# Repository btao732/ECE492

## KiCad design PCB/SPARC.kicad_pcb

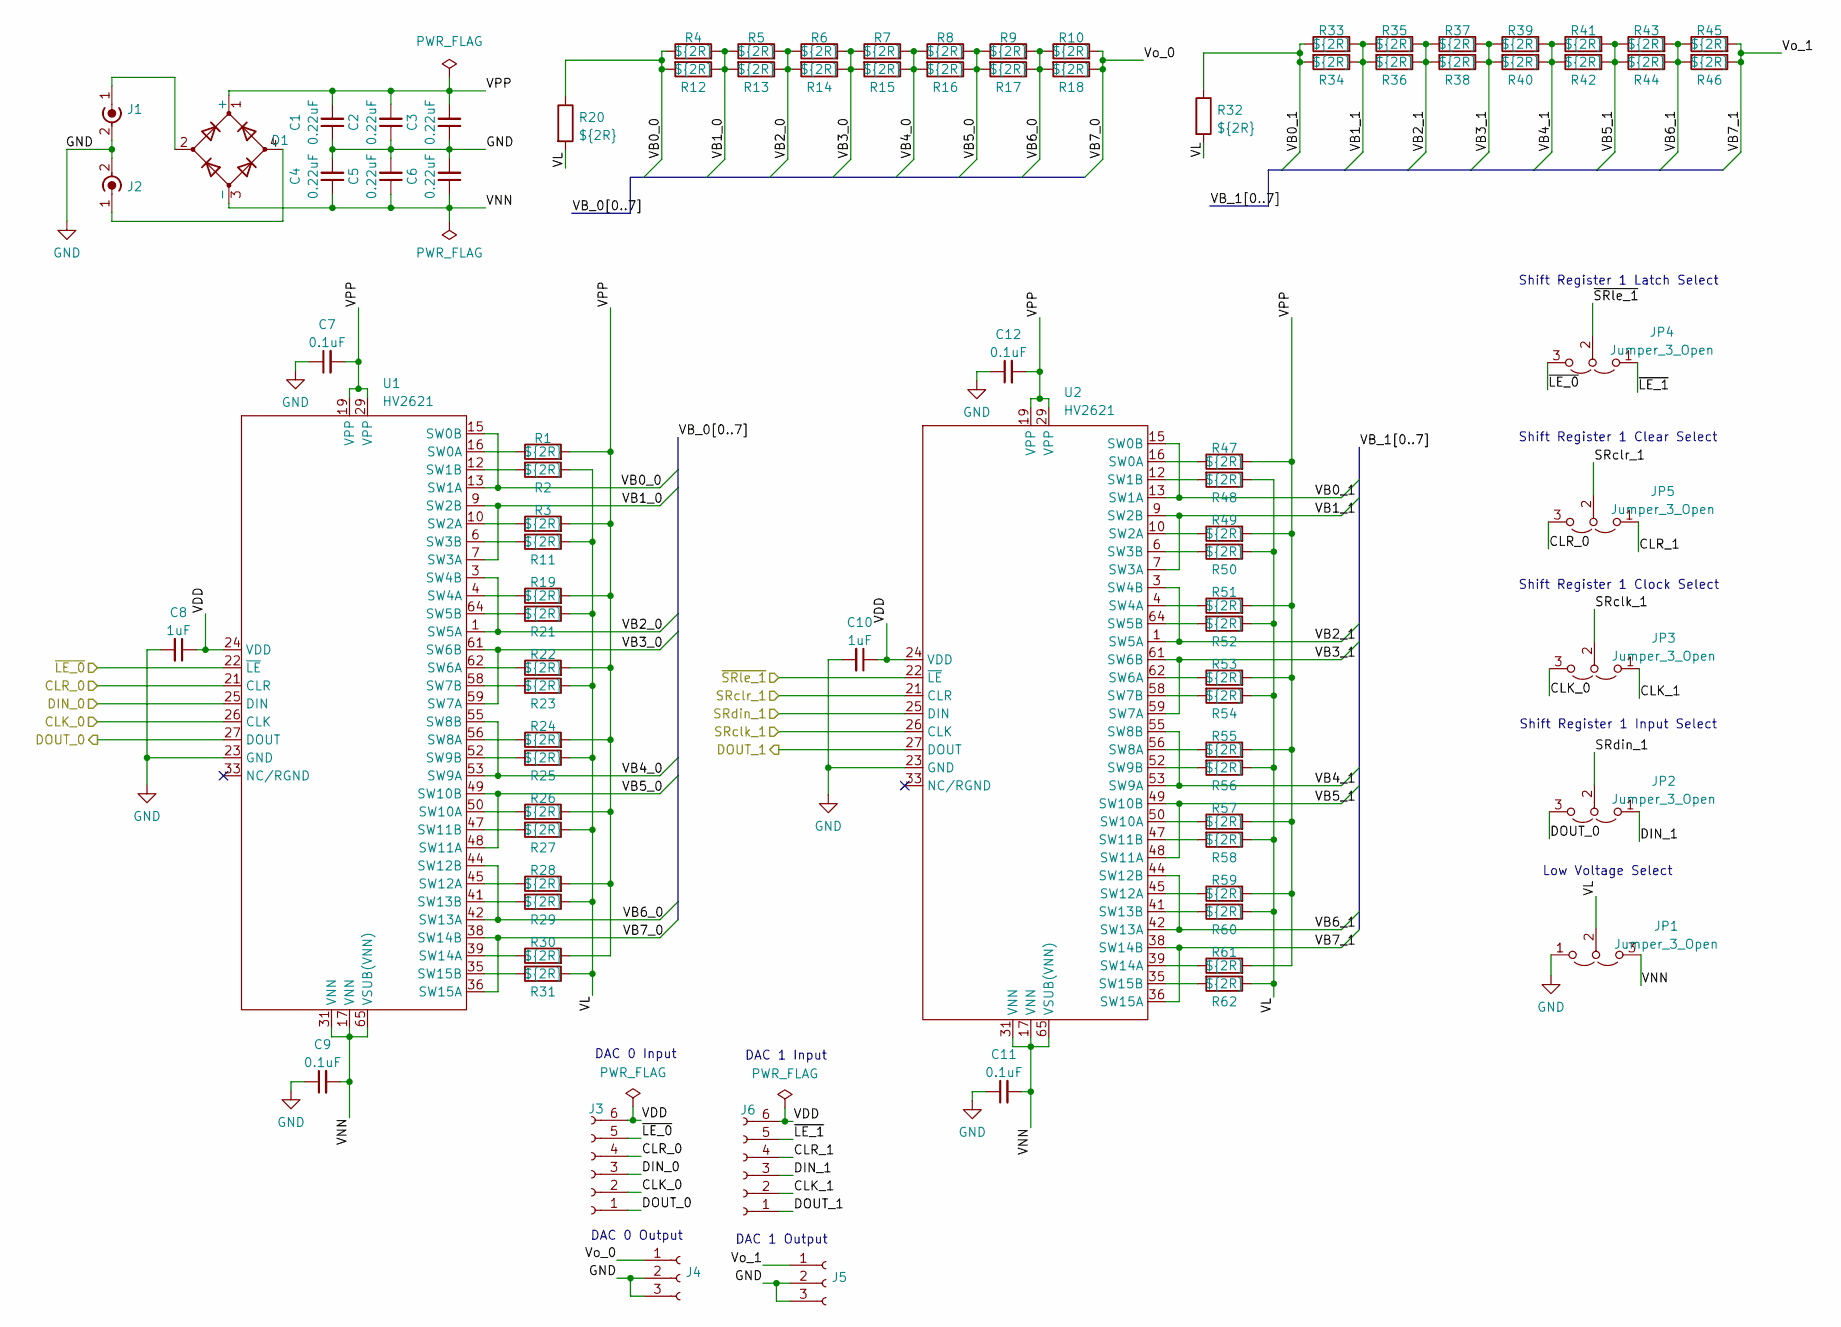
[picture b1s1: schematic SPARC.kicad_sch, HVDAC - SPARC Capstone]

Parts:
C1, C2, C3, C4, C5, C6: 0.22uF; C_1210_3225Metric
C7, C9, C11, C12: 0.1uF; C_1210_3225Metric_Pad1.33x2.70mm_HandSolder
C8, C10: 1uF; C_0603_1608Metric
D1: D_Bridge_+A-A; Package_HDS
J1, J2: Conn_Coaxial_Power; SMA_Molex_73251-1153_EdgeMount_Horizontal
J3, J6: Conn_01x06_Female; PinHeader_1x06_P2.54mm_Vertical
J4, J5: Conn_01x03_Female; PinHeader_1x03_P2.54mm_Vertical
JP1, JP2, JP3, JP4, JP5: Jumper_3_Open; PinHeader_1x03_P2.54mm_Vertical
R1, R2, R3, R4, R5, R6, R7, R8, R9, R10, R11, R12, R13, R14, R15, R16, R17, R18, R19, R20, R21, R22, R23, R24, R25, R26, R27, R28, R29, R30, R31, R32, R33, R34, R35, R36, R37, R38, R39, R40, R41, R42, R43, R44, R45, R46, R47, R48, R49, R50, R51, R52, R53, R54, R55, R56, R57, R58, R59, R60, R61, R62: ${2R}; R_0603_1608Metric_small_silk
U1, U2: HV2621; VQFN-64-1EP_9x9mm_P0.5mm_EP7.15x7.15mm_ThermalVias_0.25mm

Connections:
/CLK_0: J3.2, JP3.3 (B), U1.26 (CLK); also elsewhere on the board
/CLK_1: J6.2, JP3.1 (A); also elsewhere on the board
/CLR_0: J3.4, JP5.3 (B), U1.21 (CLR); also elsewhere on the board
/CLR_1: J6.4, JP5.1 (A); also elsewhere on the board
/DIN_0: J3.3, U1.25 (DIN)
/DIN_1: J6.3, JP2.1 (A); also elsewhere on the board
/DOUT_0: J3.1, JP2.3 (B), U1.27 (DOUT); also elsewhere on the board
/DOUT_1: J6.1, U2.27 (DOUT)
/SRclk_1: U2.26 (CLK); also elsewhere on the board
/SRclr_1: U2.21 (CLR); also elsewhere on the board
/SRdin_1: U2.25 (DIN); also elsewhere on the board
/VB0_0: R4.1, R12.2, R20.1, U1.13 (SW1A), U1.15 (SW0B)
/VB0_1: R32.1, R33.1, R34.2, U2.13 (SW1A), U2.15 (SW0B)
/VB1_0: R4.2, R5.1, R12.1, R13.2, U1.7 (SW3A), U1.9 (SW2B)
/VB1_1: R33.2, R34.1, R35.1, R36.2, U2.7 (SW3A), U2.9 (SW2B)
/VB2_0: R5.2, R6.1, R13.1, R14.2, U1.1 (SW5A), U1.3 (SW4B)
/VB2_1: R35.2, R36.1, R37.1, R38.2, U2.1 (SW5A), U2.3 (SW4B)
/VB3_0: R6.2, R7.1, R14.1, R15.2, U1.59 (SW7A), U1.61 (SW6B)
/VB3_1: R37.2, R38.1, R39.1, R40.2, U2.59 (SW7A), U2.61 (SW6B)
/VB4_0: R7.2, R8.1, R15.1, R16.2, U1.53 (SW9A), U1.55 (SW8B)
/VB4_1: R39.2, R40.1, R41.1, R42.2, U2.53 (SW9A), U2.55 (SW8B)
/VB5_0: R8.2, R9.1, R16.1, R17.2, U1.48 (SW11A), U1.49 (SW10B)
/VB5_1: R41.2, R42.1, R43.1, R44.2, U2.48 (SW11A), U2.49 (SW10B)
/VB6_0: R9.2, R10.1, R17.1, R18.2, U1.42 (SW13A), U1.44 (SW12B)
/VB6_1: R43.2, R44.1, R45.1, R46.2, U2.42 (SW13A), U2.44 (SW12B)
/VB7_0: J4.1, R10.2, R18.1, U1.36 (SW15A), U1.38 (SW14B)
/VB7_1: J5.1, R45.2, R46.1, U2.36 (SW15A), U2.38 (SW14B)
/VDD: C8.1, C10.1, J3.6, J6.6, U1.24 (VDD), U2.24 (VDD)
/VL: JP1.2 (C), R2.1, R11.1, R20.2, R21.1, R23.1, R25.1, R27.1, R29.1, R31.1, R32.2, R48.1, R50.1, R52.1, R54.1, R56.1, R58.1, R60.1, R62.1
/VNN: C4.1, C5.1, C6.1, C9.2, C11.2, D1.3 (-), JP1.3 (B), U1.17 (VNN), U1.31 (VNN), U1.65 (VSUB(VNN)), U2.17 (VNN), U2.31 (VNN), U2.65 (VSUB(VNN))
/VPP: C1.2, C2.2, C3.2, C7.2, C12.2, D1.1 (+), R1.2, R3.2, R19.2, R22.2, R24.2, R26.2, R28.2, R30.2, R47.2, R49.2, R51.2, R53.2, R55.2, R57.2, R59.2, R61.2, U1.19 (VPP), U1.29 (VPP), U2.19 (VPP), U2.29 (VPP)
/~LE_0: J3.5, JP4.3 (B), U1.22 (~LE); also elsewhere on the board
/~LE_1: J6.5, JP4.1 (A); also elsewhere on the board
/~SRle_1: U2.22 (~LE); also elsewhere on the board
GND: C1.1, C2.1, C3.1, C4.2, C5.2, C6.2, C7.1, C8.2, C9.1, C10.2, C11.1, C12.1, J1.2 (Ext), J2.2 (Ext), J4.2, J4.3, J5.2, J5.3, JP1.1 (A), U1.23 (GND), U2.23 (GND)
unnamed: D1.2, J1.1 (In)
unnamed: D1.4, J2.1 (In)
unnamed: R1.1, U1.16 (SW0A)
unnamed: R2.2, U1.12 (SW1B)
unnamed: R3.1, U1.10 (SW2A)
unnamed: R11.2, U1.6 (SW3B)
unnamed: R19.1, U1.4 (SW4A)
unnamed: R21.2, U1.64 (SW5B)
unnamed: R22.1, U1.62 (SW6A)
unnamed: R23.2, U1.58 (SW7B)
unnamed: R24.1, U1.56 (SW8A)
unnamed: R25.2, U1.52 (SW9B)
unnamed: R26.1, U1.50 (SW10A)
unnamed: R27.2, U1.47 (SW11B)
unnamed: R28.1, U1.45 (SW12A)
unnamed: R29.2, U1.41 (SW13B)
unnamed: R30.1, U1.39 (SW14A)
unnamed: R31.2, U1.35 (SW15B)
unnamed: R47.1, U2.16 (SW0A)
unnamed: R48.2, U2.12 (SW1B)
unnamed: R49.1, U2.10 (SW2A)
unnamed: R50.2, U2.6 (SW3B)
unnamed: R51.1, U2.4 (SW4A)
unnamed: R52.2, U2.64 (SW5B)
unnamed: R53.1, U2.62 (SW6A)
unnamed: R54.2, U2.58 (SW7B)
unnamed: R55.1, U2.56 (SW8A)
unnamed: R56.2, U2.52 (SW9B)
unnamed: R57.1, U2.50 (SW10A)
unnamed: R58.2, U2.47 (SW11B)
unnamed: R59.1, U2.45 (SW12A)
unnamed: R60.2, U2.41 (SW13B)
unnamed: R61.1, U2.39 (SW14A)
unnamed: R62.2, U2.35 (SW15B)

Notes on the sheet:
DAC 1 Output
Low Voltage Select
DAC 0 Output
Shift Register 1 Clear Select
Shift Register 1 Latch Select
DAC 1 Input
DAC 0 Input
Shift Register 1 Input Select
Shift Register 1 Clock Select

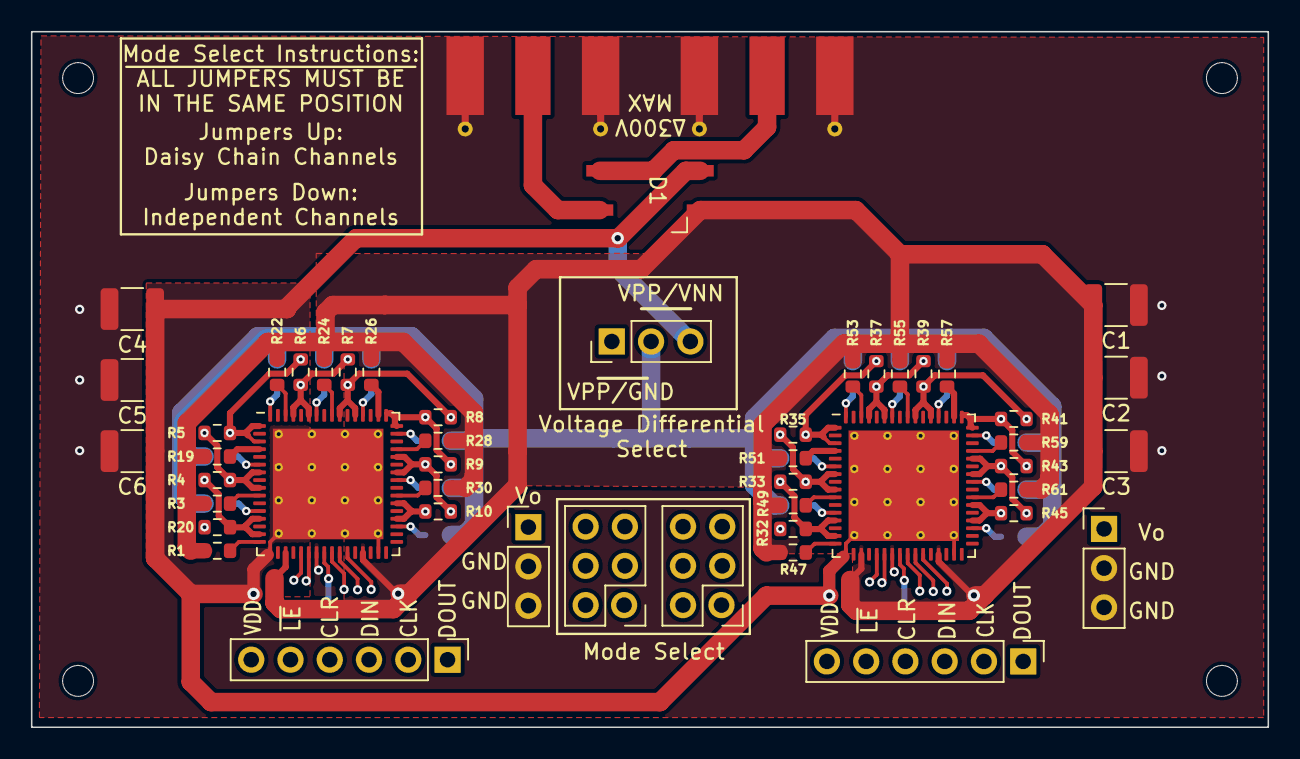
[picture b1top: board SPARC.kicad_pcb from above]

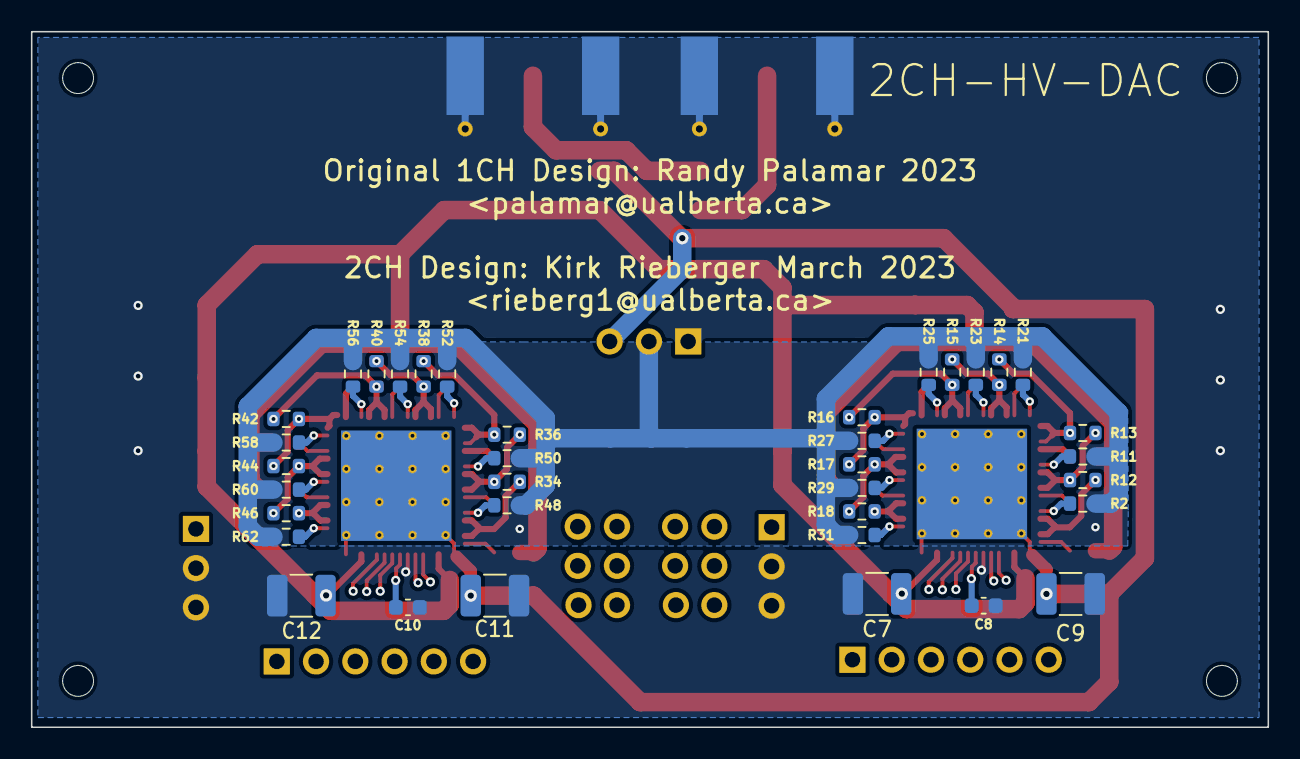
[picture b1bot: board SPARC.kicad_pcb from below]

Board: 4 copper layers, 80.0 x 45.0 mm, 86 parts (36 on the bottom side), 69 nets.

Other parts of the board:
JP3 JP2, JP4 JP5: PinHeader_2x03_P2.54mm_Vertical

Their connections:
/CLK_0: JP3 JP2.6; also elsewhere on the board
/CLK_1: JP3 JP2.2; also elsewhere on the board
/CLR_0: JP4 JP5.5; also elsewhere on the board
/CLR_1: JP4 JP5.1; also elsewhere on the board
/DIN_1: JP3 JP2.1; also elsewhere on the board
/DOUT_0: JP3 JP2.5; also elsewhere on the board
/SRclk_1: JP3 JP2.4; also elsewhere on the board
/SRclr_1: JP4 JP5.3; also elsewhere on the board
/SRdin_1: JP3 JP2.3; also elsewhere on the board
/~LE_0: JP4 JP5.6; also elsewhere on the board
/~LE_1: JP4 JP5.2; also elsewhere on the board
/~SRle_1: JP4 JP5.4; also elsewhere on the board

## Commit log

2023-01-30 Added ECE492
2023-01-30 Update ECE492
2023-01-30 add an actor
2023-01-31 serial monitor
2023-01-31 vivado project added
2023-02-01 VHDL PISO register implemented, testbench included
2023-02-03 PISO controller added
2023-02-07 updating system design
2023-02-10 update system architecture
2023-02-10 update color
2023-02-10 Update modules
2023-02-16 Software Diagram.drawio
2023-02-17 Added SoftwareFigure.drawio
2023-02-17 Added FirmwareFigure.drawio
2023-03-03 Init commit
2023-03-03 Fixed prices and references
2023-03-03 Added PCB KiCad Project
2023-03-03 Updated gitignore for KiCad
2023-03-03 Add files via upload
    convert text file to binary file
2023-03-03 serial monitor update
2023-03-04 Worked on adding second channel
2023-03-04 Worked on fillers
2023-03-05 stuff
2023-03-05 more stuff
2023-03-05 lookup table
2023-03-05 voltage encoding
2023-03-05 comments
2023-03-05 math header included
2023-03-05 formatting
2023-03-06 waveform binary generation
2023-03-06 binary file generation for one channel
2023-03-06 bug fix
2023-03-06 matlab compatibility
2023-03-06 matlab C++ code gen function
2023-03-06 waveform gen for multiple channels
2023-03-07 makefile
2023-03-07 added C++ MATLAB engine
2023-03-07 removed test
2023-03-07 test
2023-03-07 Changed resistors and added jumpers
2023-03-08 Finished traces, finalized board
2023-03-08 Updated BOM
2023-03-08 matlab library
2023-03-08 Added BOM
2023-03-08 Updated R20 & R32 connection
2023-03-08 Updated R20 & R32 routing
2023-03-09 Reworked mode select jumpers
2023-03-09 Updated BOM to optimize costs
2023-03-09 Re-compressed project folder
2023-03-09 Closing the project changed some things
2023-03-09 Removed extraneous BOM
2023-03-09 Updated BOMs
2023-03-09 Updated 3D model for HV2621
2023-03-15 Updated Gerbers
2023-03-15 Modified design rules
    Fixed tracks based on PCBWay fab capabilities
2023-03-17 Changed silkscreen
2023-03-18 Changed schematic layout
2023-03-22 DMA system
2023-04-03 Changed mockup colour to match real board
2023-04-08 Add files via upload
    DMA loopback test simple mode
